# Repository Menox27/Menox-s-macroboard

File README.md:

# Menox-s-macroboard

This is my personal Macroboard controlled by a XIAO R2040. I redid it multiple times and this is the final version I am quite proud of. thanks to @Simon who helped me alot and thanks to whom I was able to improve my skills drasticly.
It got 9 keys, each with RGB-LEDs, a rotary encoder and a 0.91 OLED. This macroboard will be used to improve my workflow and just add more features to my setup.<br>

<br>

Schematic: <br>
This is the schematic. I split all the seperate components into diffrent wiring groups:<br>

PCB:<br>
This is how I connected everything. It´s a little bit messy but I tried to keep it as straight forward as possible, only used 4 vias in the whole projekt and added a little bit of spongebob art.
In case you are wondering about the setup: The XIAO is mounted on the back so the OLED can be placed right above it on the frontside<br>

Case:<br>
This is the case I came up with. It has a layer to mount the switches and one to hide the OLEDs parts that I dont want to be seen.<br>

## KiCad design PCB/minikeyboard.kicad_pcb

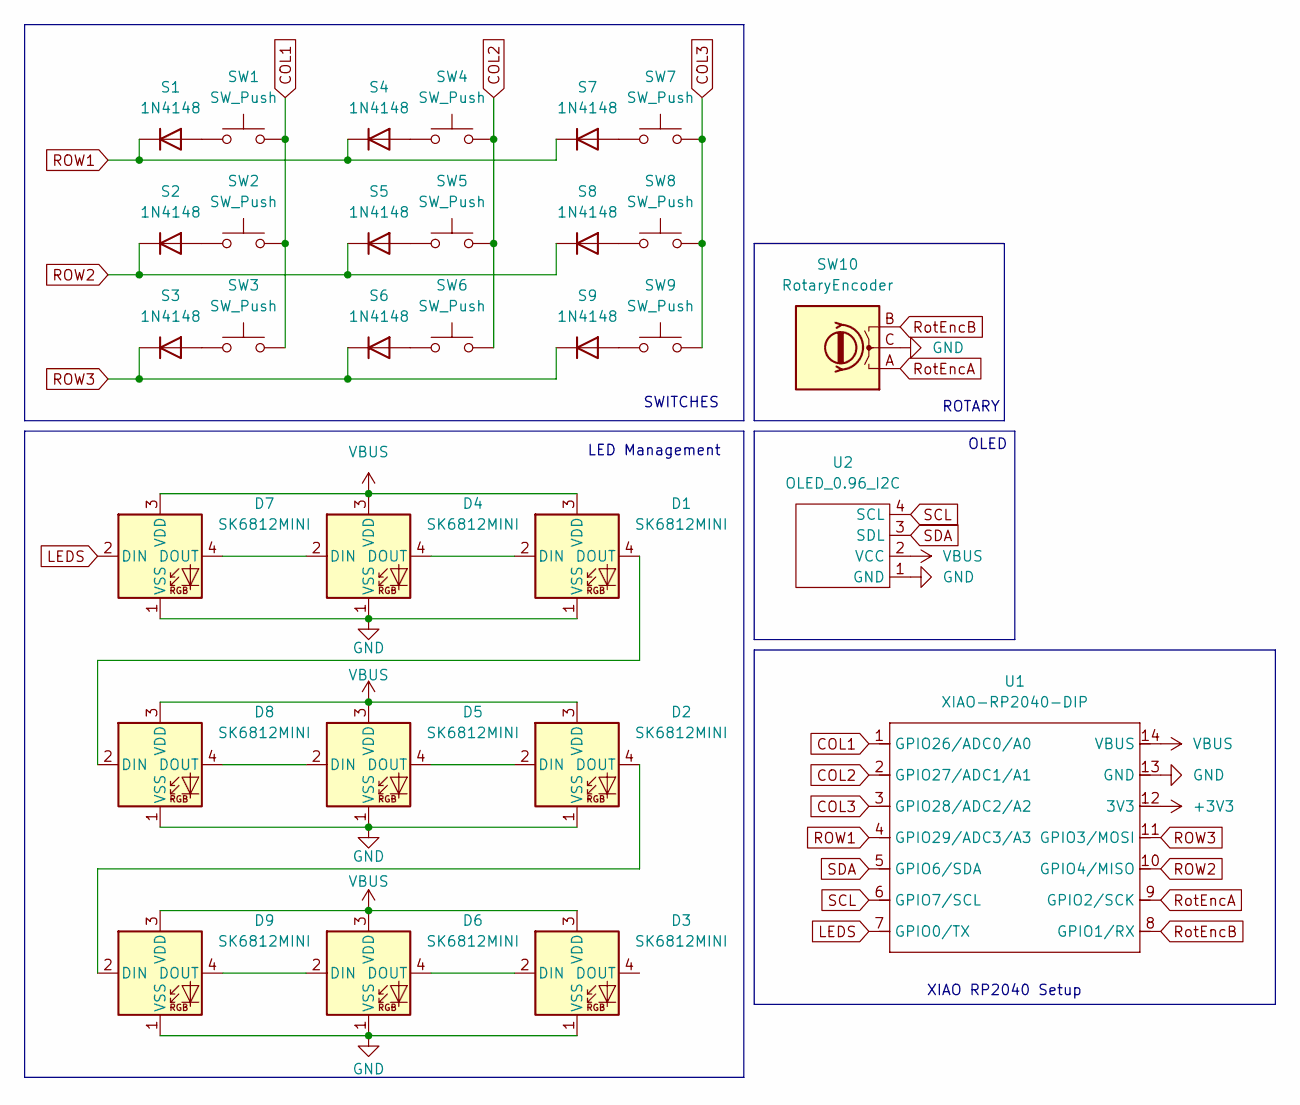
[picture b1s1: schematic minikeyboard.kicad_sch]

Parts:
D1, D2, D3, D4, D5, D6, D7, D8, D9: SK6812MINI; LED_SK6812MINI-E_PLCC4_3.2x2.8mm_P1.5mm
S1, S2, S3, S4, S5, S6, S7, S8, S9: 1N4148; D_DO-35_SOD27_P7.62mm_Horizontal
SW1, SW2, SW3, SW4, SW5, SW6, SW7, SW8, SW9: SW_Push; SW_Cherry_MX_1.00u_PCB
SW10: RotaryEncoder; RotaryEncoder_Alps_EC11E_Vertical_H20mm
U1: XIAO-RP2040-DIP
U2: OLED_0.96_I2C; SSD1306-0.91-OLED-4pin-128x32

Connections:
+3V3: U1.12 (3V3)
COL1: SW1.2, SW2.2, SW3.2, U1.1 (GPIO26/ADC0/A0)
COL2: SW4.2, SW5.2, SW6.2, U1.2 (GPIO27/ADC1/A1)
COL3: SW7.2, SW8.2, SW9.2, U1.3 (GPIO28/ADC2/A2)
GND: D1.1 (VSS), D2.1 (VSS), D3.1 (VSS), D4.1 (VSS), D5.1 (VSS), D6.1 (VSS), D7.1 (VSS), D8.1 (VSS), D9.1 (VSS), SW10.C, U1.13 (GND), U2.1 (GND)
LEDS: D7.2 (DIN), U1.7 (GPIO0/TX)
unnamed: D1.2 (DIN), D4.4 (DOUT)
unnamed: D1.4 (DOUT), D8.2 (DIN)
unnamed: D2.2 (DIN), D5.4 (DOUT)
unnamed: D2.4 (DOUT), D9.2 (DIN)
unnamed: D3.2 (DIN), D6.4 (DOUT)
unnamed: D4.2 (DIN), D7.4 (DOUT)
unnamed: D5.2 (DIN), D8.4 (DOUT)
unnamed: D6.2 (DIN), D9.4 (DOUT)
unnamed: S1.2 (A), SW1.1
unnamed: S2.2 (A), SW2.1
unnamed: S3.2 (A), SW3.1
unnamed: S4.2 (A), SW4.1
unnamed: S5.2 (A), SW5.1
unnamed: S6.2 (A), SW6.1
unnamed: S7.2 (A), SW7.1
unnamed: S8.2 (A), SW8.1
unnamed: S9.2 (A), SW9.1
ROW1: S1.1 (K), S4.1 (K), S7.1 (K), U1.4 (GPIO29/ADC3/A3)
ROW2: S2.1 (K), S5.1 (K), S8.1 (K), U1.10 (GPIO4/MISO)
ROW3: S3.1 (K), S6.1 (K), S9.1 (K), U1.11 (GPIO3/MOSI)
RotEncA: SW10.A, U1.9 (GPIO2/SCK)
RotEncB: SW10.B, U1.8 (GPIO1/RX)
SCL: U1.6 (GPIO7/SCL), U2.4 (SCL)
SDA: U1.5 (GPIO6/SDA), U2.3 (SDL)
VBUS: D1.3 (VDD), D2.3 (VDD), D3.3 (VDD), D4.3 (VDD), D5.3 (VDD), D6.3 (VDD), D7.3 (VDD), D8.3 (VDD), D9.3 (VDD), U1.14 (VBUS), U2.2 (VCC)

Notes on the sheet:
SWITCHES
OLED
ROTARY
XIAO RP2040 Setup
LED Management

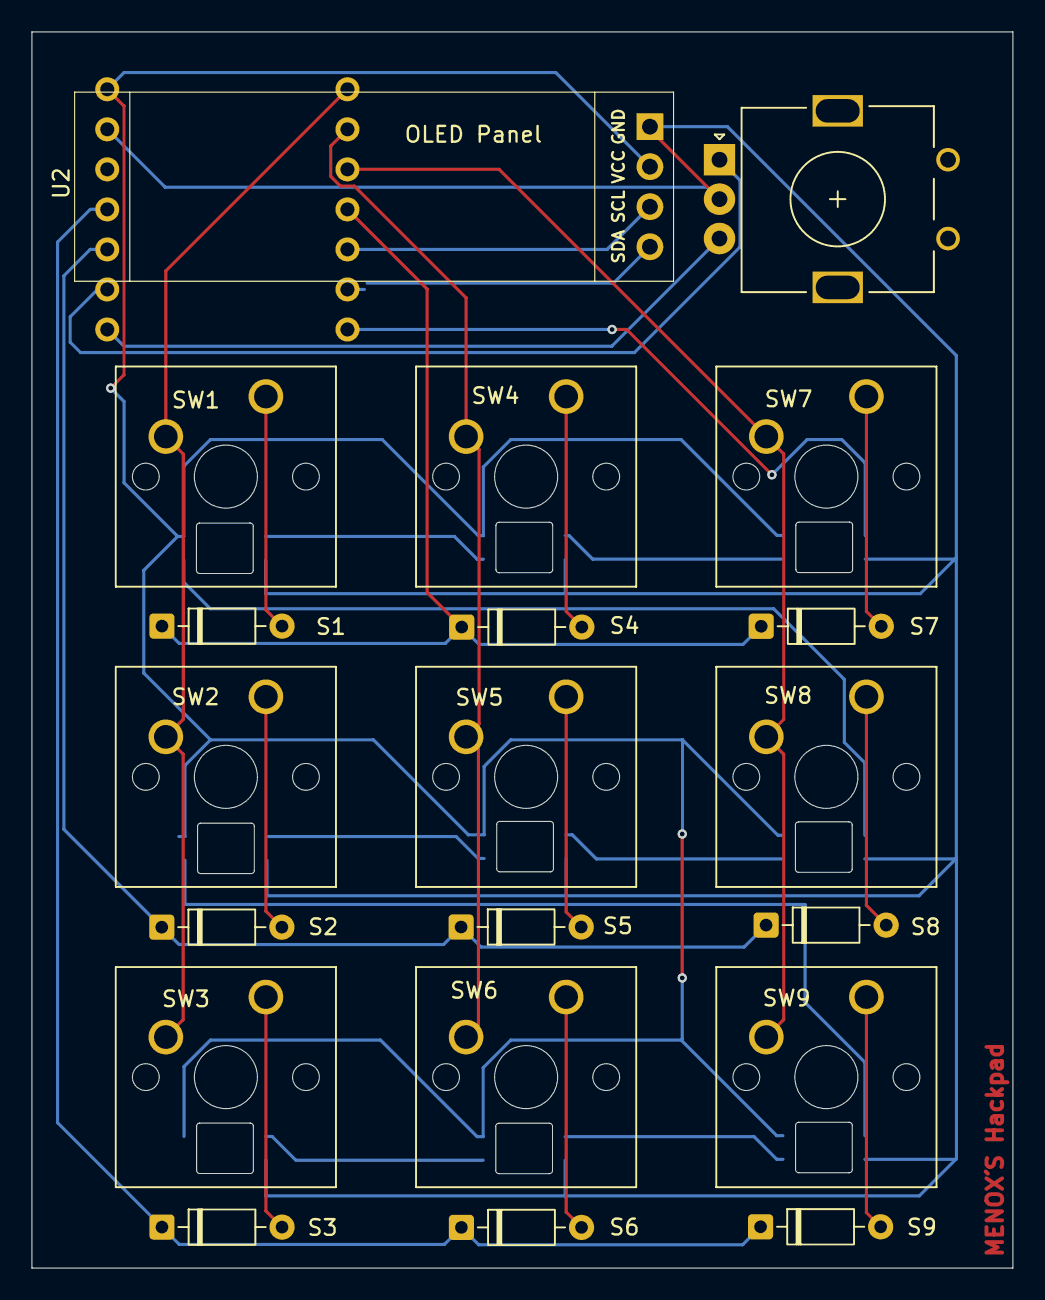
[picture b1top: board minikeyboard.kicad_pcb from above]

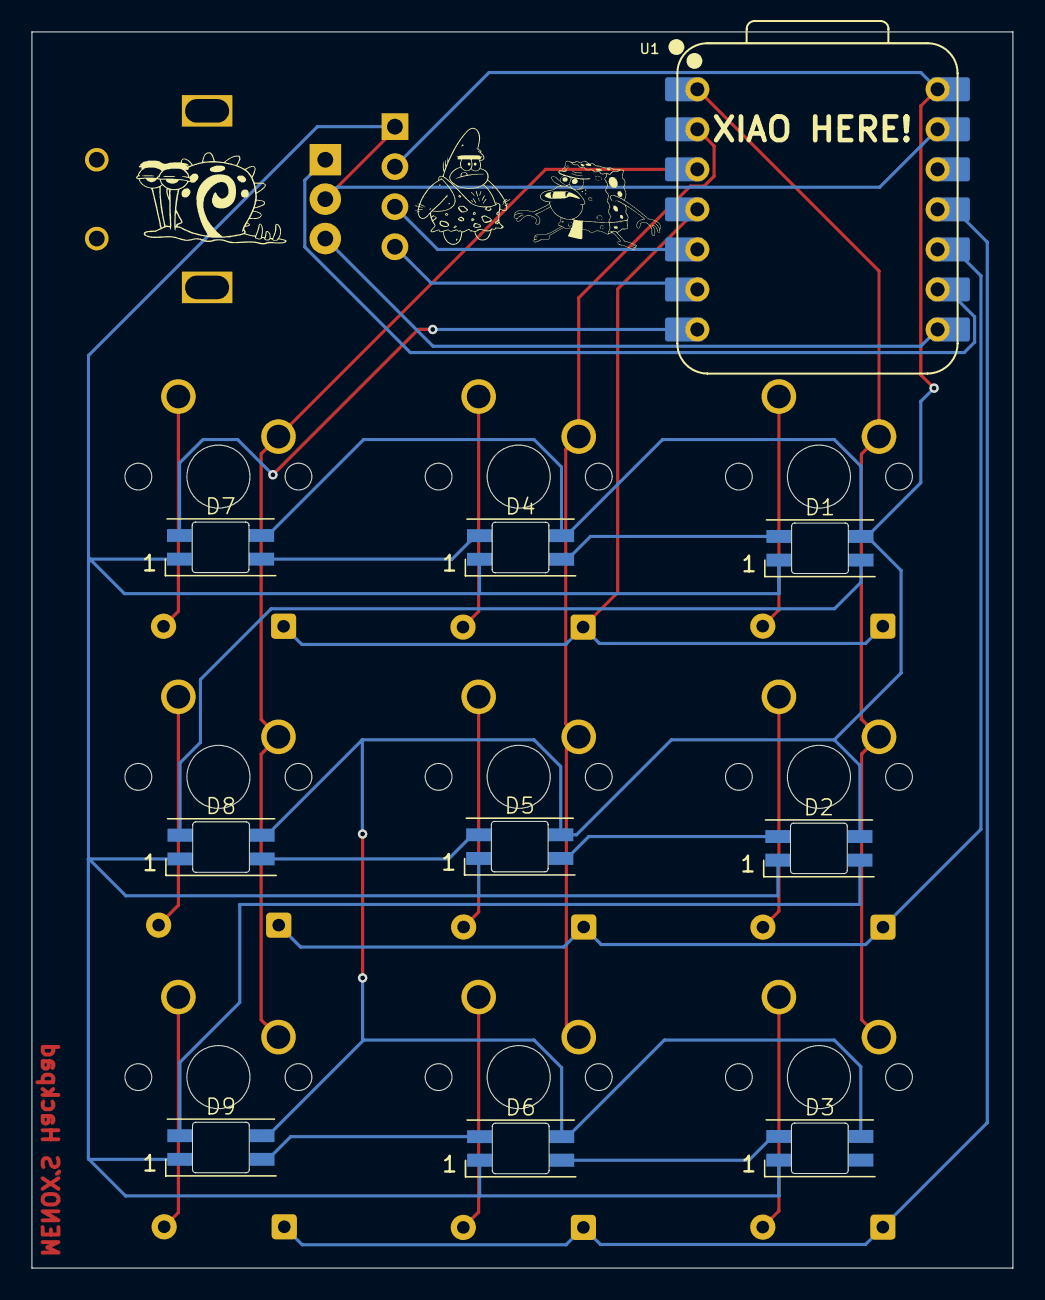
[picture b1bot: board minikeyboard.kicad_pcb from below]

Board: 2 copper layers, 62.2 x 78.4 mm, 30 parts (10 on the bottom side), 30 nets.

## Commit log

2025-12-22 Fix typo in README description
    Corrected a typo in the project description.
2025-12-22 Update README to specify XIAO-RP2040 macroboard
2025-12-22 adding the files
2025-12-25 firmware
    kmk file as well as my config file
2025-12-25 new case with PCB inside
2025-12-25 cleanup
2025-12-25 Enhance README with project details and images
    Added detailed descriptions, images, and BOM for the macroboard.
2026-01-05 Complete overhaul of the layout, parts and case
    for better use and higher quality
2026-01-05 Error-fixing
    Had to reupload the PCB due to wrong placement of "XIAO here" (B.Cu instead B.Silkscreen)
2026-01-05 Revise README with detailed macroboard description
    Updated the README to provide a more detailed description of the macroboard, including its features and components. Added images and improved clarity of the schematic, PCB, and case sections.
2026-01-05 final update with all correct files
    Finished the Macroboard after a few long nights 😄
    Still very fun project! would recommend trying it urself
2026-01-05 Refactor README for better readability
    Updated the README to improve formatting and clarity.
2026-01-05 Refactor README for improved readability
    Updated README to enhance formatting and clarity.
2026-01-05 Revise BOM format to include costs in a table
    Updated the Bill of Materials (BOM) format to a table with costs.
2026-01-05 Remove BOM section from README.md
    Removed BOM section from the README. Will add a BOM.csv
2026-01-05 Add BOM.csv with bill of materials
2026-01-06 adding the single files
